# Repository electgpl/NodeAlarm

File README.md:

# 🔔 Wireless Alarm Sensor with ESP32-C3 + RFM69 + PIR (AS312)

This project consists of an ultra-low-power wireless motion sensor based on an **ESP32-C3**, an **RFM69 transceiver** in the 926 MHz FSK band, and an **AS312 PIR sensor** as the main detector.

Designed with an **Open Source Hardware** philosophy, powered by a **3V CR123 cell**, and aimed at low-power, long-life security, monitoring, and home automation applications.

---

## 📸 Top View of the PCB

---

## 📡 Specs

- **MCU:** ESP32-C3 (RISC-V, Wi-Fi, BLE)
- **Transceiver:** RFM69 (FSK, 926 MHz, point-to-point or custom network)
- **Sensor PIR:** AS312 (interrupt mode, ultra-low power consumption)
- **Low power mode:** DeepSleep, waking up by IRQ
- **Standby consumption:** < 30 µA
- **Power supply:** 3V CR123 battery
- **Manufacturing PCBA:** NextPCB
- **Open Hardware:** License CERN-OHL v2
- **Firmware:** PlatformIO / Arduino Framework

---

## 🔋 Estimated consumption

| State          | Typical consumption |
|----------------|---------------------|
| DeepSleep      | ~24 µA              |
| PIR & CORE     |  ~9 mA by 5s        |
| TX RFM69       | ~18 mA by 1.5s      |

---

This repository is released under a dual-license model:

---

## 📐 Hardware (KiCad designs)

**License:** [CERN Open Hardware License v2](https://ohwr.org/project/cernohl/wikis/home)

You are free to use, study, modify and distribute the hardware files, provided that:
- Derivative works are also released under CERN-OHL v2.
- Modifications are documented.
- Attribution is preserved.

---

## 💻 Firmware (source code under `/firmware/`)

**License:** MIT License

```text
MIT License

Copyright (c) 2025 Electgpl

Permission is hereby granted, free of charge, to any person obtaining a copy
of this software and associated documentation files (the “Software”), to deal
in the Software without restriction, including without limitation the rights to
use, copy, modify, merge, publish, distribute, sublicense, and/or sell copies
of the Software, and to permit persons to whom the Software is furnished to do
so, subject to the following conditions.

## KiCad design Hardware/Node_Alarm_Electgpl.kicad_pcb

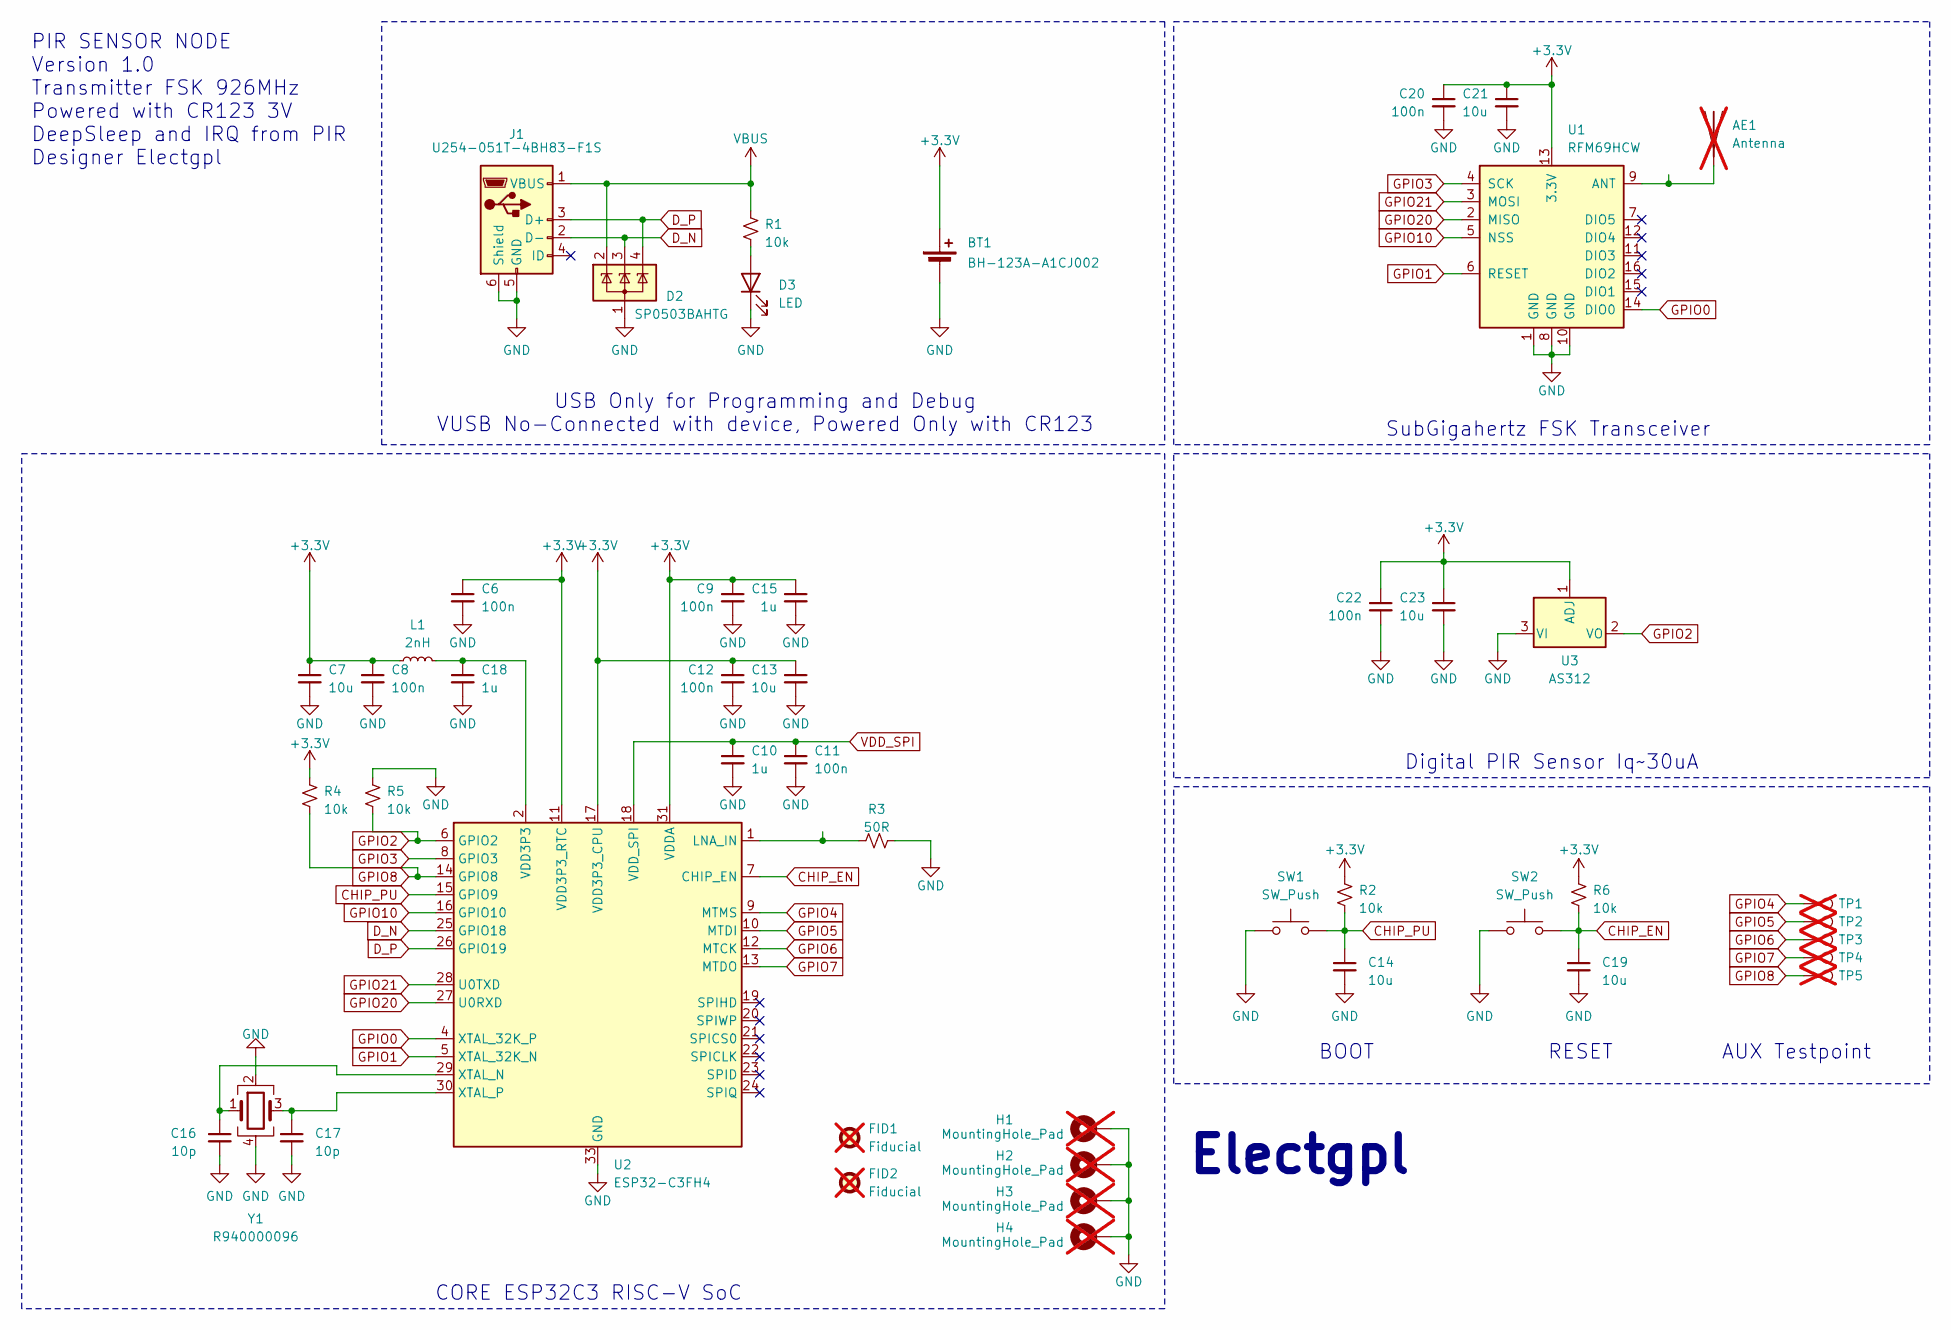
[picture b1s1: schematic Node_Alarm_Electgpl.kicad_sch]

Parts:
AE1: Antenna; Texas_SWRA416_868MHz_915MHz; not fitted
BT1: BH-123A-A1CJ002; BatteryHolder_Bulgin_BX0123_1xCR123; LCSC C5290177
C6, C8, C9, C11, C12, C20, C22: 100n; C_0603_1608Metric; MFR P/N CC0402KRX7R9BB104; LCSC C14663
C7, C13, C14, C19, C21, C23: 10u; C_0603_1608Metric; MFR P/N GCM188D70J106ME36D; LCSC C85713
C10, C15, C18: 1u; C_0603_1608Metric; MFR P/N CL05X105KP5NNNC; LCSC C1592
C16, C17: 10p; C_0603_1608Metric; MFR P/N GRM1555C1H100GA01D; LCSC C106245
D2: SP0503BAHTG; SOT-143; MFR P/N SP0503BAHTG; LCSC C7074
D3: LED; LED_0603_1608Metric; MFR P/N TJ-S1608B06HQYJY-A3; LCSC C965799
FID1, FID2: Fiducial; Fiducial_1mm_Mask2mm; not fitted
H1, H2, H3, H4: MountingHole_Pad; MountingHole_3.2mm_M3_Pad_Via; not fitted
J1: U254-051T-4BH83-F1S; USB_Micro-B_XKB_U254-051T-4BH83-F1S; MFR P/N U254-051T-4BH83-F1S; LCSC C397452
L1: 2nH; L_0603_1608Metric; LCSC C395081
R1, R2, R4, R5, R6: 10k; R_0603_1608Metric; MFR P/N RC0402JR-0710KL; LCSC C98220
R3: 50R; R_0603_1608Metric; MFR P/N RT0603BRE0750RL; LCSC C849792
SW1, SW2: SW_Push; SW_Push_SPST_NO_Alps_SKRK; MFR P/N SKRKAEE020; LCSC C115357
TP1, TP2, TP3, TP4, TP5: TestPoint; TestPoint_Pad_D2.0mm; not fitted
U1: RFM69HCW; HOPERF_RFM9XW_SMD; LCSC ?
U2: ESP32-C3FH4; QFN-32-1EP_5x5mm_P0.5mm_EP3.7x3.7mm; LCSC C2858491
U3: AS312; TO-39-3; LCSC C90465
Y1: R940000096; Crystal_SMD_2016-4Pin_2.0x1.6mm; MFR P/N TAXM40M4ZHBCDT2T; LCSC C7206306

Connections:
+3.3V: BT1.1 (+), C6.1, C7.1, C8.1, C9.1, C12.1, C13.1, C15.1, C20.1, C21.1, C22.1, C23.1, L1.1, R2.1, R4.1, R6.1, U1.13 (3.3V), U2.11 (VDD3P3_RTC), U2.17 (VDD3P3_CPU), U2.31 (VDDA), U2.32 (VDDA), U3.1 (ADJ)
CHIP_EN: C19.1, R6.2, SW2.2, U2.7 (CHIP_EN)
CHIP_PU: C14.1, R2.2, SW1.2, U2.15 (GPIO9)
D_N: D2.3 (K), J1.2 (D-), U2.25 (GPIO18)
D_P: D2.4 (K), J1.3 (D+), U2.26 (GPIO19)
GND: BT1.2 (-), C6.2, C7.2, C8.2, C9.2, C10.2, C11.2, C12.2, C13.2, C14.2, C15.2, C16.2, C17.2, C18.2, C19.2, C20.2, C21.2, C22.2, C23.2, D2.1 (A), D3.1 (K), H1.1, H2.1, H3.1, H4.1, J1.5 (GND), J1.6 (Shield), R3.2, R5.1, SW1.1, SW2.1, U1.1 (GND), U1.8 (GND), U1.10 (GND), U2.33 (GND), U3.3 (VI), Y1.2, Y1.4
GPIO0: U1.14 (DIO0), U2.4 (XTAL_32K_P)
GPIO1: U1.6 (RESET), U2.5 (XTAL_32K_N)
GPIO2: R5.2, U2.6 (GPIO2), U3.2 (VO)
GPIO3: U1.4 (SCK), U2.8 (GPIO3)
GPIO4: TP1.1, U2.9 (MTMS)
GPIO5: TP2.1, U2.10 (MTDI)
GPIO6: TP3.1, U2.12 (MTCK)
GPIO7: TP4.1, U2.13 (MTDO)
GPIO8: R4.2, TP5.1, U2.14 (GPIO8)
GPIO10: U1.5 (NSS), U2.16 (GPIO10)
GPIO20: U1.2 (MISO), U2.27 (U0RXD)
GPIO21: U1.3 (MOSI), U2.28 (U0TXD)
unnamed: AE1.1 (A), U1.9 (ANT)
unnamed: C18.1, L1.2, U2.2 (VDD3P3), U2.3 (VDD3P3)
unnamed: D3.2 (A), R1.2
unnamed: R3.1, U2.1 (LNA_IN)
unnamed: C16.1, U2.29 (XTAL_N), Y1.1
unnamed: C17.1, U2.30 (XTAL_P), Y1.3
VBUS: D2.2 (K), J1.1 (VBUS), R1.1
VDD_SPI: C10.1, C11.1, U2.18 (VDD_SPI)

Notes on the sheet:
AUX Testpoint
Electgpl
CORE ESP32C3 RISC-V SoC
USB Only for Programming and Debug VUSB No-Connected with device, Powered Only with CR123
PIR SENSOR NODE Version 1.0 Transmitter FSK 926MHz Powered with CR123 3V DeepSleep and IRQ from PIR Designer Electgpl
BOOT
Digital PIR Sensor Iq~30uA
SubGigahertz FSK Transceiver
RESET

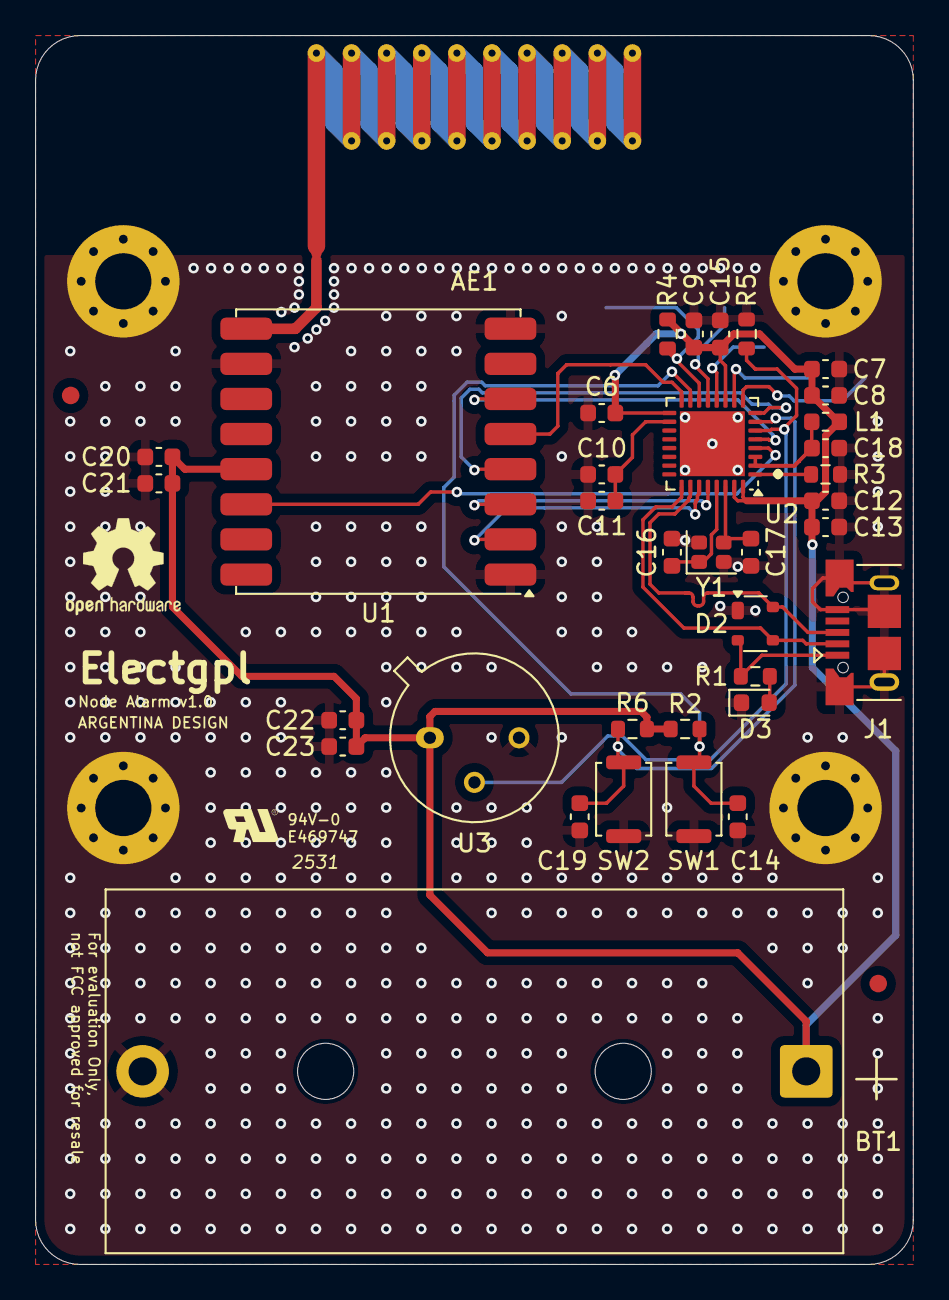
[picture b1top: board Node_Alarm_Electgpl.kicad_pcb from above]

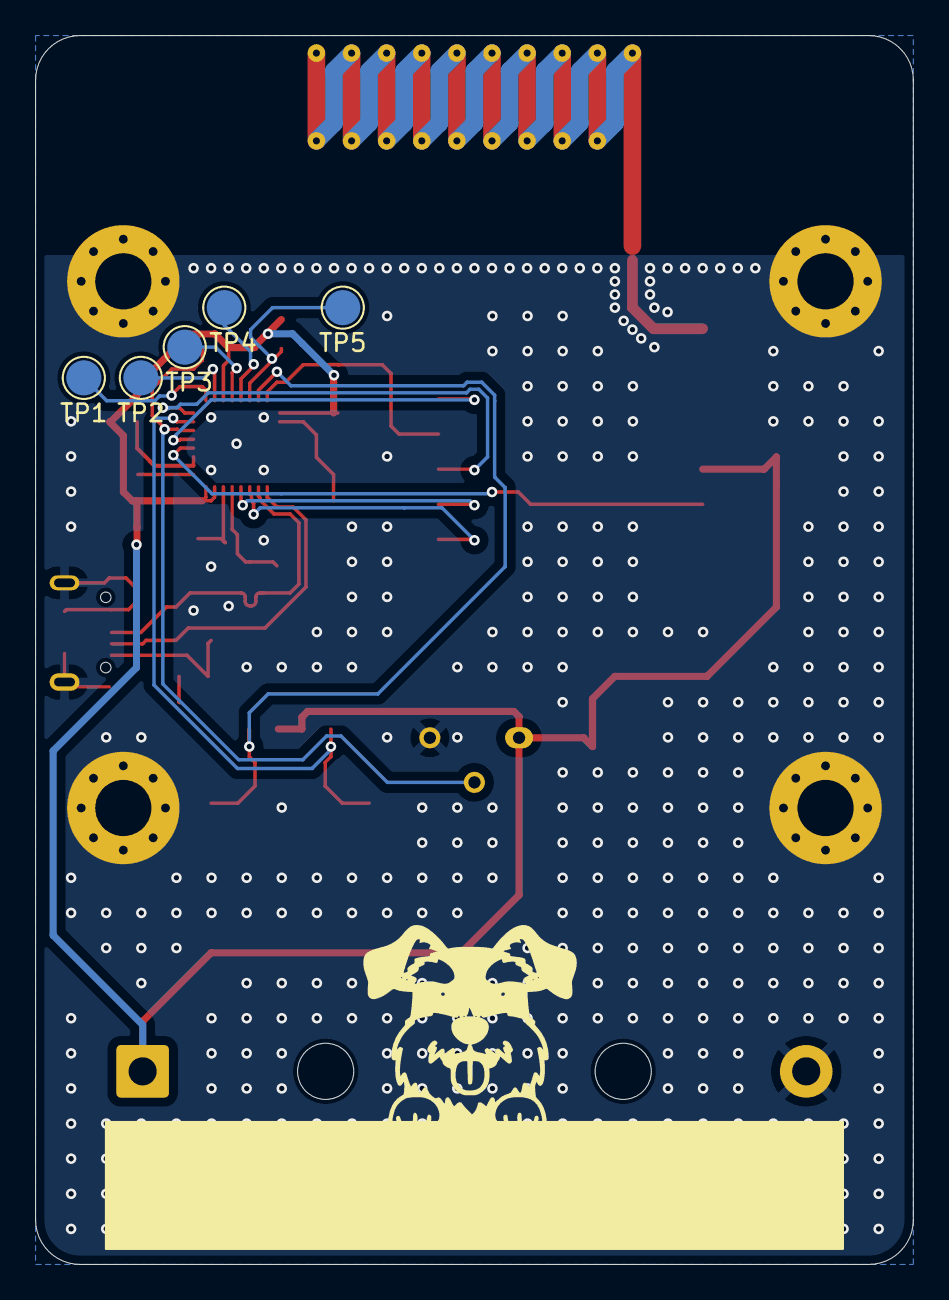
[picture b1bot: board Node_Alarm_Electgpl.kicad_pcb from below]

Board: 2 copper layers, 50.0 x 70.0 mm, 47 parts (5 on the bottom side), 26 nets.
